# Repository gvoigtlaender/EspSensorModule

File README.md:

# EspSensorModule
## Attiny, Reed-Relay, ESP8266, DTH

## Project goals:
* timed meassurement of Temperature & Humidity
* battery driven (18650) with internal voltage meassurement
* small footprint
* optional display of status
* publish values via mqtt

## Items on store:
* ESP8266 microcontroller with wifi
* DTH11 / DTH22 temperature sensor
* ATtiny ultra low power microcontroller for timer-control
* 1A05 REED Relays
* SSD1306 128x32px OLED display
* BC846 npn transistor

## Schema:

## PCB:

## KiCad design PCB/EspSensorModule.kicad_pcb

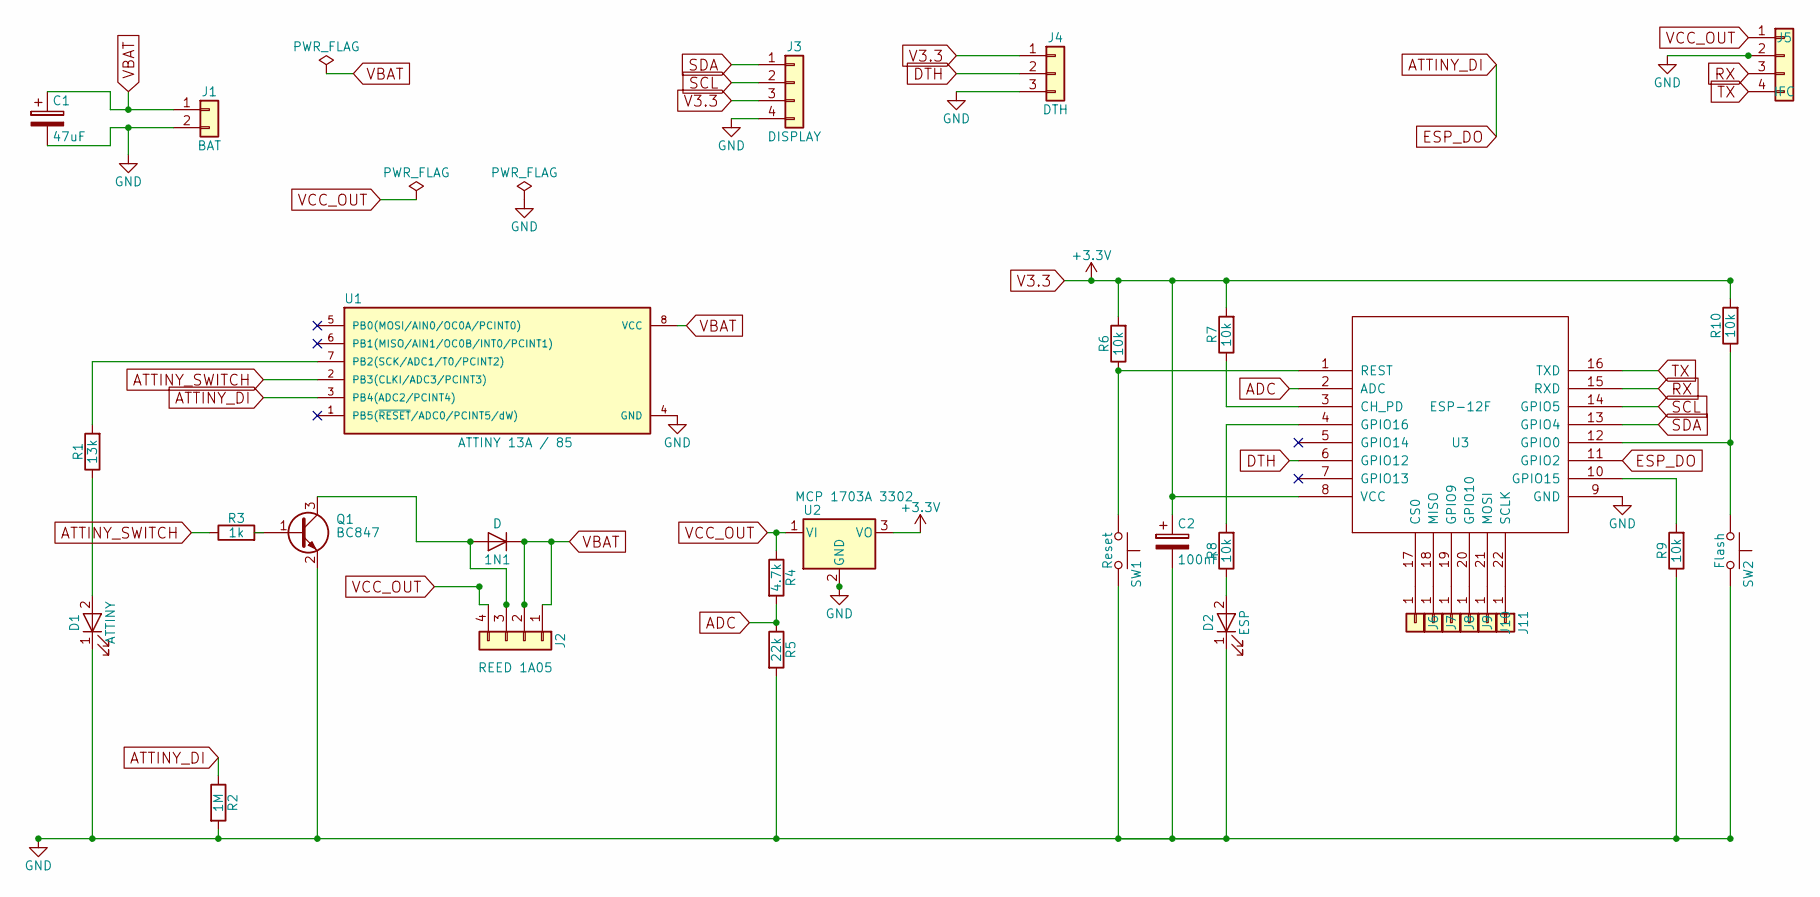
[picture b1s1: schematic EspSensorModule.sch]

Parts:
1N1: D; D_SMA_Handsoldering
C1: 47uF; CP_Radial_D4.0mm_P2.00mm
C2: 100nF; CP_Radial_D4.0mm_P2.00mm
D1: ATTINY; LED_0805_HandSoldering
D2: ESP; LED_0805_HandSoldering
J1: BAT; Pin_Header_Straight_1x02_Pitch2.54mm
J2: REED 1A05; Relay_Reed
J3: DISPLAY; Pin_Header_Straight_1x04_Pitch2.54mm
J4: DTH; Socket_Strip_Straight_1x03_Pitch2.54mm
J5: IFC; Pin_Header_Angled_1x04_Pitch2.54mm
J6, J7, J8, J9, J10, J11: TestPin
Q1: BC847; SOT-23
R1: 13k; R_0805_HandSoldering
R2: 1M; R_0805_HandSoldering
R3: 1k; R_0805_HandSoldering
R4: 4.7k; R_0805_HandSoldering
R5: 22k; R_0805_HandSoldering
R6, R7, R8, R9, R10: 10k; R_0805_HandSoldering
SW1: Reset; SW_SPST_TL3342
SW2: Flash; SW_SPST_TL3342
U1: ATTINY 13A / 85; SOP-SOIC-8_3.9x4.9mm_Pitch1.27mm
U2: MCP 1703A 3302; SOT-223-3Lead_TabPin2
U3: ESP-12F; ESP-12E_SMD

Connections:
ADC: R4.2, R5.1, U3.2 (ADC)
ATTINY_DI: R2.1, U1.3 (PB4(ADC2/PCINT4)), U3.11 (GPIO2)
ATTINY_SWITCH: R3.1, U1.2 (PB3(CLKI/ADC3/PCINT3))
DTH: J4.2, U3.6 (GPIO12)
GND: C1.2, C2.2, D1.1 (K), D2.1 (K), J1.2, J3.4, J4.3, J5.2, Q1.2 (E), R2.2, R5.2, R9.1, SW1.2, SW2.2, U1.4 (GND), U2.2 (GND), U3.9 (GND)
unnamed: 1N1.2 (A), J2.3, Q1.3 (C)
unnamed: D1.2 (A), R1.1
unnamed: D2.2 (A), R8.1
unnamed: J6.1, U3.17 (CS0)
unnamed: J7.1, U3.18 (MISO)
unnamed: J8.1, U3.19 (GPIO9)
unnamed: J9.1, U3.20 (GPIO10)
unnamed: J10.1, U3.21 (MOSI)
unnamed: J11.1, U3.22 (SCLK)
unnamed: Q1.1 (B), R3.2
unnamed: R1.2, U1.7 (PB2(SCK/ADC1/T0/PCINT2))
unnamed: R6.1, SW1.1, U3.1 (REST)
unnamed: R7.1, U3.3 (CH_PD)
unnamed: R8.2, U3.4 (GPIO16)
unnamed: R9.2, U3.10 (GPIO15)
unnamed: R10.1, SW2.1, U3.12 (GPIO0)
RX: J5.3, U3.15 (RXD)
SCL: J3.2, U3.14 (GPIO5)
SDA: J3.1, U3.13 (GPIO4)
TX: J5.4, U3.16 (TXD)
V3.3: C2.1, J3.3, J4.1, R6.2, R7.2, R10.2, U2.3 (VO), U3.8 (VCC)
VBAT: 1N1.1 (K), C1.1, J1.1, J2.1, J2.2, U1.8 (VCC)
VCC_OUT: J2.4, J5.1, R4.1, U2.1 (VI)

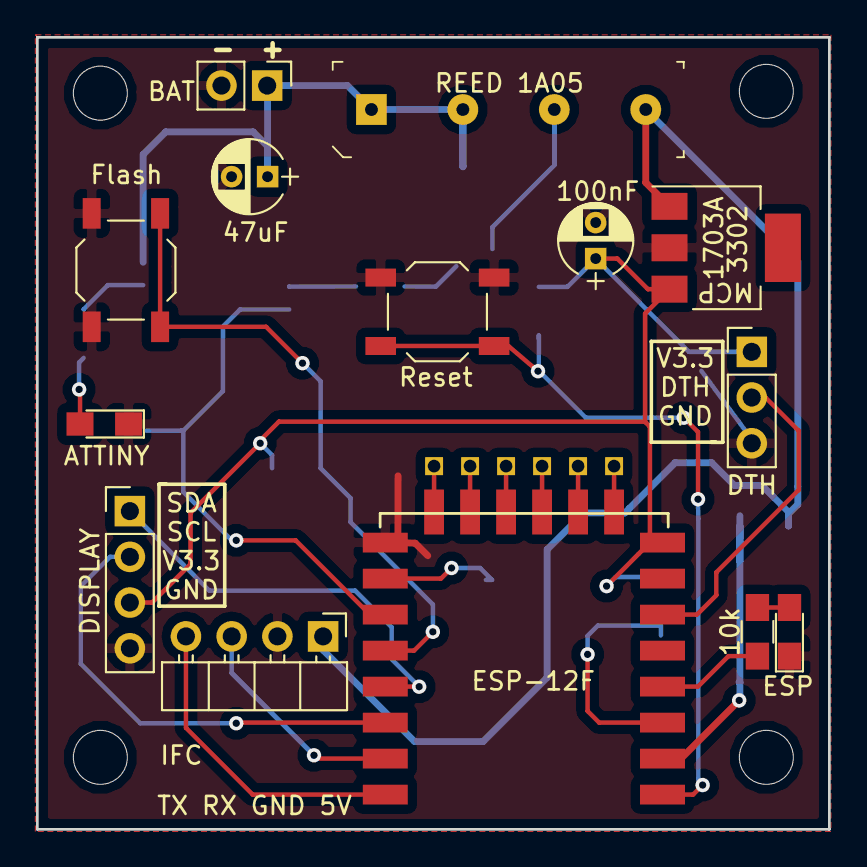
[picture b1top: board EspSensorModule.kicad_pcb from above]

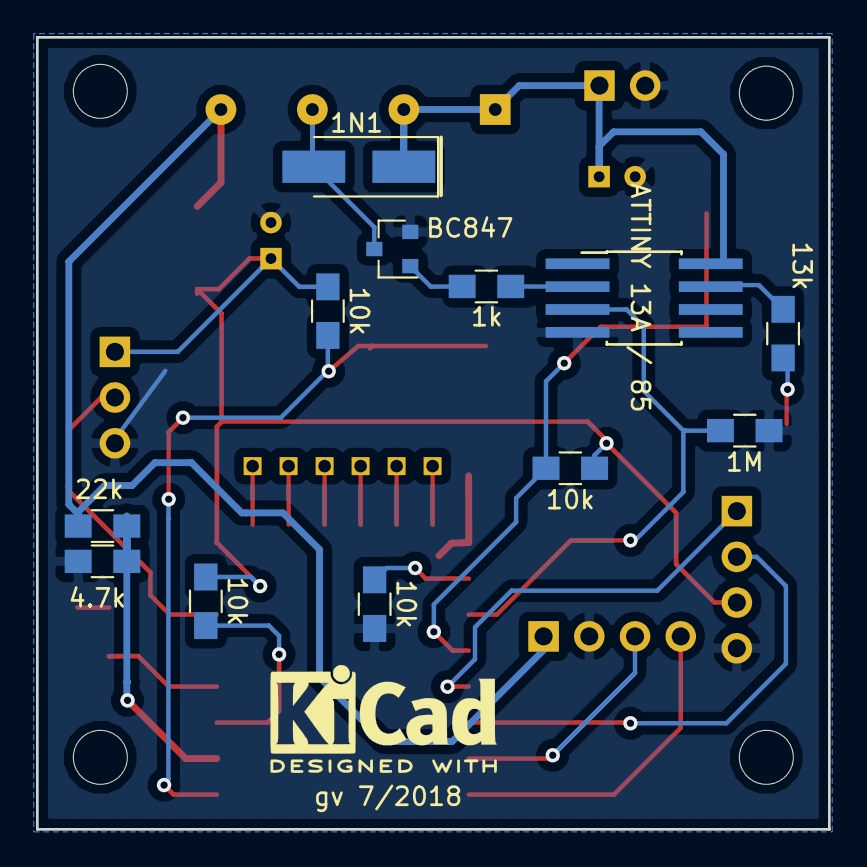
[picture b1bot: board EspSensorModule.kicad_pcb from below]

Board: 2 copper layers, 44.0 x 44.0 mm, 36 parts (12 on the bottom side), 28 nets.

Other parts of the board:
REF01, REF2, REF3, REF4: MountingHole_3mm

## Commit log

2018-08-20 library dependencies
2018-08-21 add config template
2018-08-21 build configuration
2018-08-21 make static ip optional
2018-09-08 Mutliple configuration (Attiny13 & 85
2022-07-08 rename
